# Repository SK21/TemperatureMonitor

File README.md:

# TemperatureMonitor

Temperature Monitor reads temperatures from DS18B20 sensors in grain bins. It consists of a server and multiple clients (controlboxes). The server is installed on a PC on the LAN. Each controlbox sends data over wifi to the server. On startup if a network connection can't be made a web page is started at 192.168.4.1 . 
  
Hookup Schematic:
</img> 

TMarduino can use a DS2482 1-Wire Master. It is a device to connect to 1-Wire networks for improved performance. A DS2482 breakout is available at https://www.artekit.eu/products/breakout-boards/io/ak-ds2482s-100/

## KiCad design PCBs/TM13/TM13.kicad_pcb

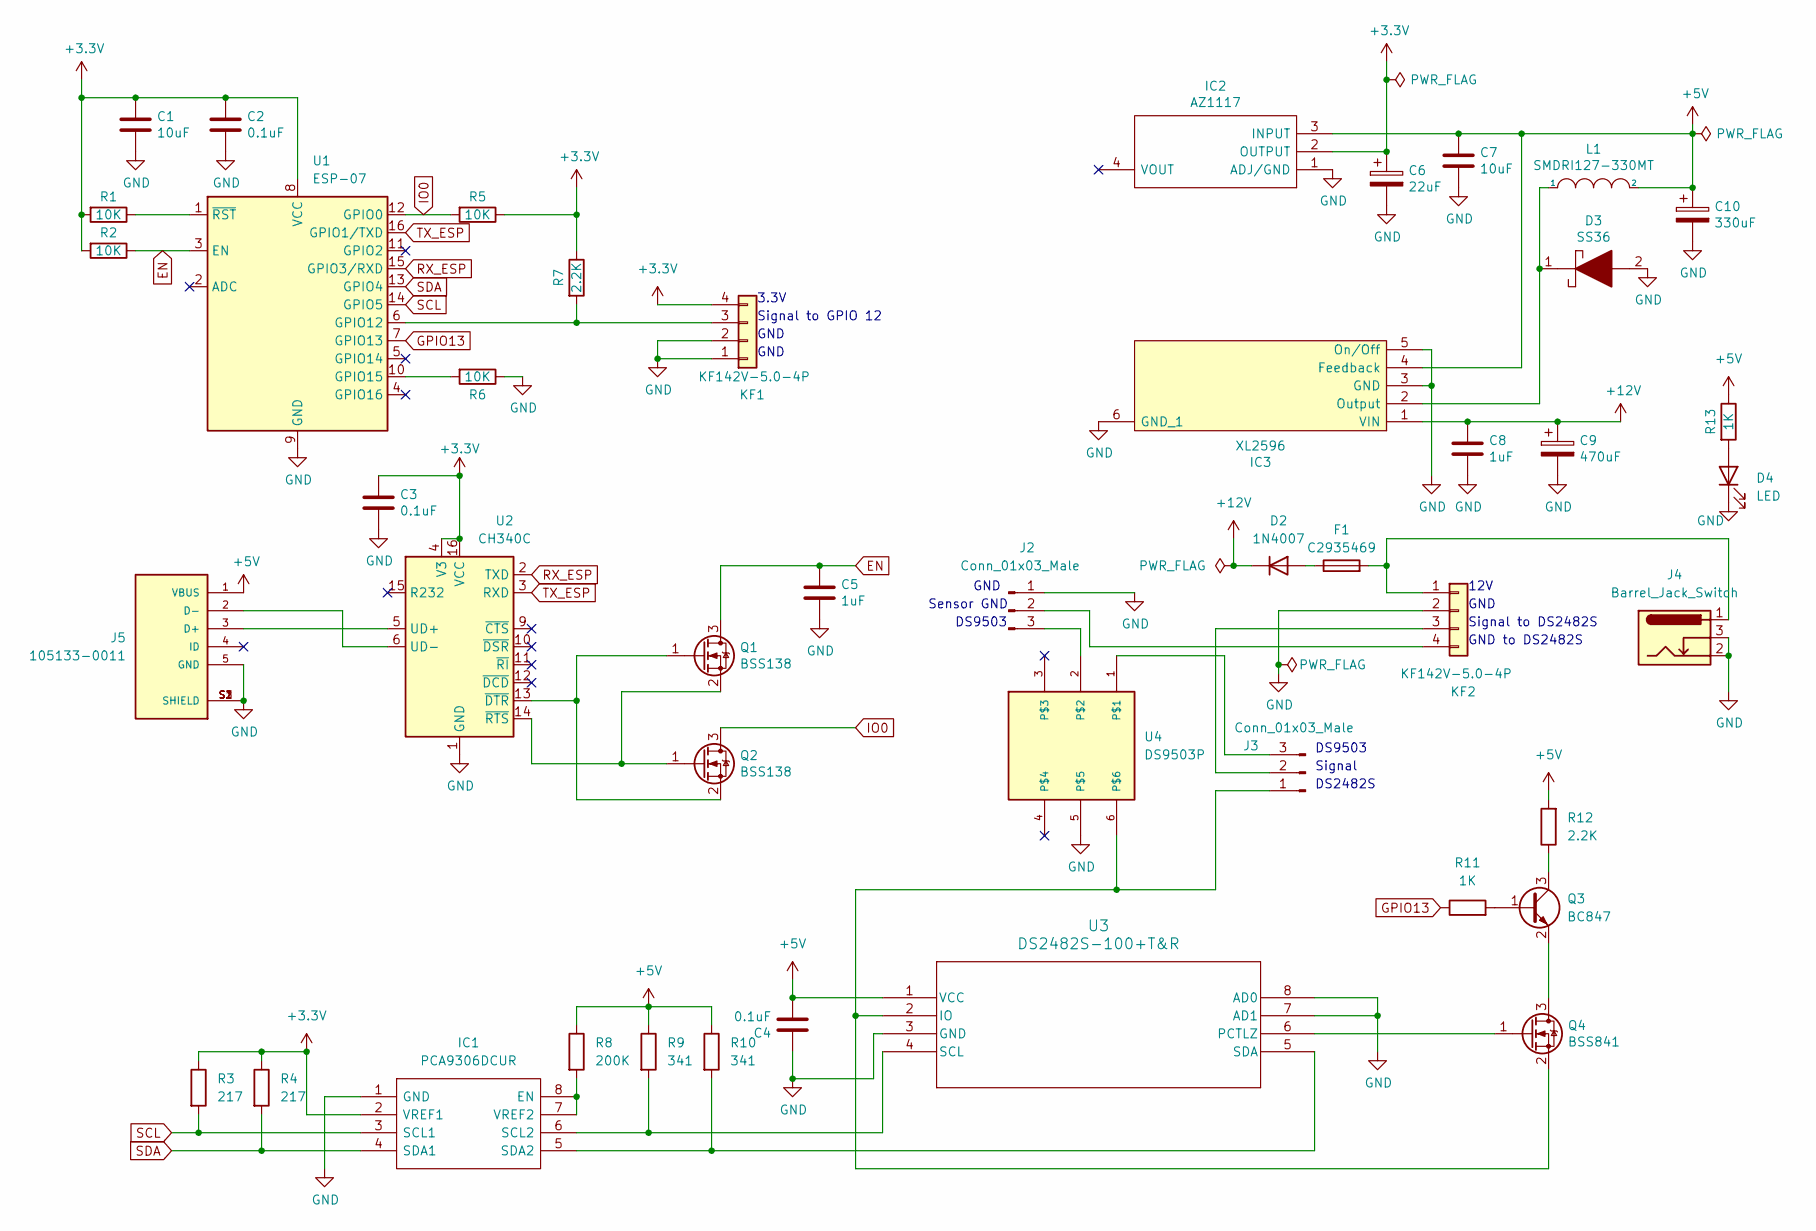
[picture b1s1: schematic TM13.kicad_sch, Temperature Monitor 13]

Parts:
C1, C7: 10uF; C_0805_2012Metric
C2, C3, C4: 0.1uF; C_0805_2012Metric
C5, C8: 1uF; C_0805_2012Metric
C6: 22uF; C_0805_2012Metric
C9: 470uF; CP_Elec_10x10.5
C10: 330uF; CP_Elec_10x10.5
D2: 1N4007; D_SMA
D3: SS36; SMA(DO-214AC)
D4: LED; LED_0805_2012Metric
F1: C2935469; Fuse_Holder_C2935469
IC1: PCA9306DCUR; Mouser Part Number 595-PCA9306DCUR
IC2: AZ1117; SOT230P700X180-4N; Mouser Part Number 621-AZ1117CH-3.3TRG1
IC3: XL2596; TO263-5L
J2, J3: Conn_01x03_Male; PinHeader_1x03_P2.54mm_Vertical
J4: Barrel_Jack_Switch; BarrelJack_Wuerth_6941xx301002
J5: 105133-0011; MOLEX_105133-0011; PARTREV C
KF1, KF2: KF142V-5.0-4P; KF142V-5.08-4P
L1: SMDRI127-330MT; TMPA1265SP-101MN-D
Q1, Q2: BSS138; SOT-23
Q3: BC847; SOT-23
Q4: BSS841; SOT-23
R1, R2, R5, R6: 10K; R_0603_1608Metric
R3, R4: 217; R_0603_1608Metric
R7, R12: 2.2K; R_0603_1608Metric
R8: 200K; R_0603_1608Metric
R9, R10: 341; R_0603_1608Metric
R11, R13: 1K; R_0603_1608Metric
U1: ESP-07; ESP-07S
U2: CH340C; SOIC-16_3.9x9.9mm_P1.27mm
U3: DS2482S-100+T&R; 21-0041B_8_MXM
U4: DS9503P; TSO6C

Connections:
+3.3V: C1.1, C2.1, C3.1, C6.1, IC1.2 (VREF1), IC2.2 (OUTPUT), KF1.4, R1.2, R2.2, R3.1, R4.1, R5.1, R7.1, U1.8 (VCC), U2.4 (V3), U2.16 (VCC)
+5V: C4.2, C7.1, C10.1, IC2.3 (INPUT), IC3.4 (Feedback), J5.1 (VBUS), L1.2, R8.1, R9.1, R10.1, R12.2, R13.1, U3.1 (VCC)
+12V: C8.1, C9.1, D2.1 (K), IC3.1 (VIN)
EN: C5.1, Q1.3 (D), R2.1, U1.3 (EN)
GND: C1.2, C2.2, C3.2, C4.1, C5.2, C6.2, C7.2, C8.2, C9.2, C10.2, D3.2, D4.1 (K), IC1.1 (GND), IC2.1 (ADJ/GND), IC3.3 (GND), IC3.5 (On/Off), IC3.6 (GND_1), J2.1, J4.2, J4.3, J5.5 (GND), J5.S1 (SHIELD), J5.S2 (SHIELD), J5.S3 (SHIELD), KF1.1, KF1.2, KF2.2, R6.1, U1.9 (GND), U2.1 (GND), U3.3 (GND), U3.7 (AD1), U3.8 (AD0), U4.5
GPIO13: R11.1, U1.7 (GPIO13)
IO0: Q2.3 (D), R5.2, U1.12 (GPIO0)
unnamed: D2.2 (A), F1.1
unnamed: D4.2 (A), R13.2
unnamed: IC1.7 (VREF2), IC1.8 (EN), R8.2
unnamed: IC1.6 (SCL2), R9.2, U3.4 (SCL)
unnamed: IC1.5 (SDA2), R10.2, U3.5 (SDA)
unnamed: D3.1, IC3.2 (Output), L1.1
unnamed: J2.2, KF2.4
unnamed: J2.3, U4.2
unnamed: J3.1, Q4.2 (S), U3.2 (IO), U4.6
unnamed: J3.2, KF2.3
unnamed: J3.3, U4.1
unnamed: J5.3 (D+), U2.5 (UD+)
unnamed: J5.2 (D-), U2.6 (UD-)
unnamed: KF1.3, R7.2, U1.6 (GPIO12)
unnamed: F1.2, J4.1, KF2.1
unnamed: Q1.1 (G), Q2.2 (S), U2.13 (~DTR)
unnamed: Q1.2 (S), Q2.1 (G), U2.14 (~RTS)
unnamed: Q3.1 (B), R11.2
unnamed: Q3.3 (C), R12.1
unnamed: Q3.2 (E), Q4.3 (D)
unnamed: Q4.1 (G), U3.6 (PCTLZ)
unnamed: R6.2, U1.10 (GPIO15)
unnamed: R1.1, U1.1 (~RST)
RX_ESP: U1.15 (GPIO3/RXD), U2.2 (TXD)
SCL: IC1.3 (SCL1), R3.2, U1.14 (GPIO5)
SDA: IC1.4 (SDA1), R4.2, U1.13 (GPIO4)
TX_ESP: U1.16 (GPIO1/TXD), U2.3 (RXD)

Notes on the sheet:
Signal to DS2482S
Sensor GND
GND
DS9503
DS2482S
Signal
12V
GND to DS2482S
Signal to GPIO 12
3.3V

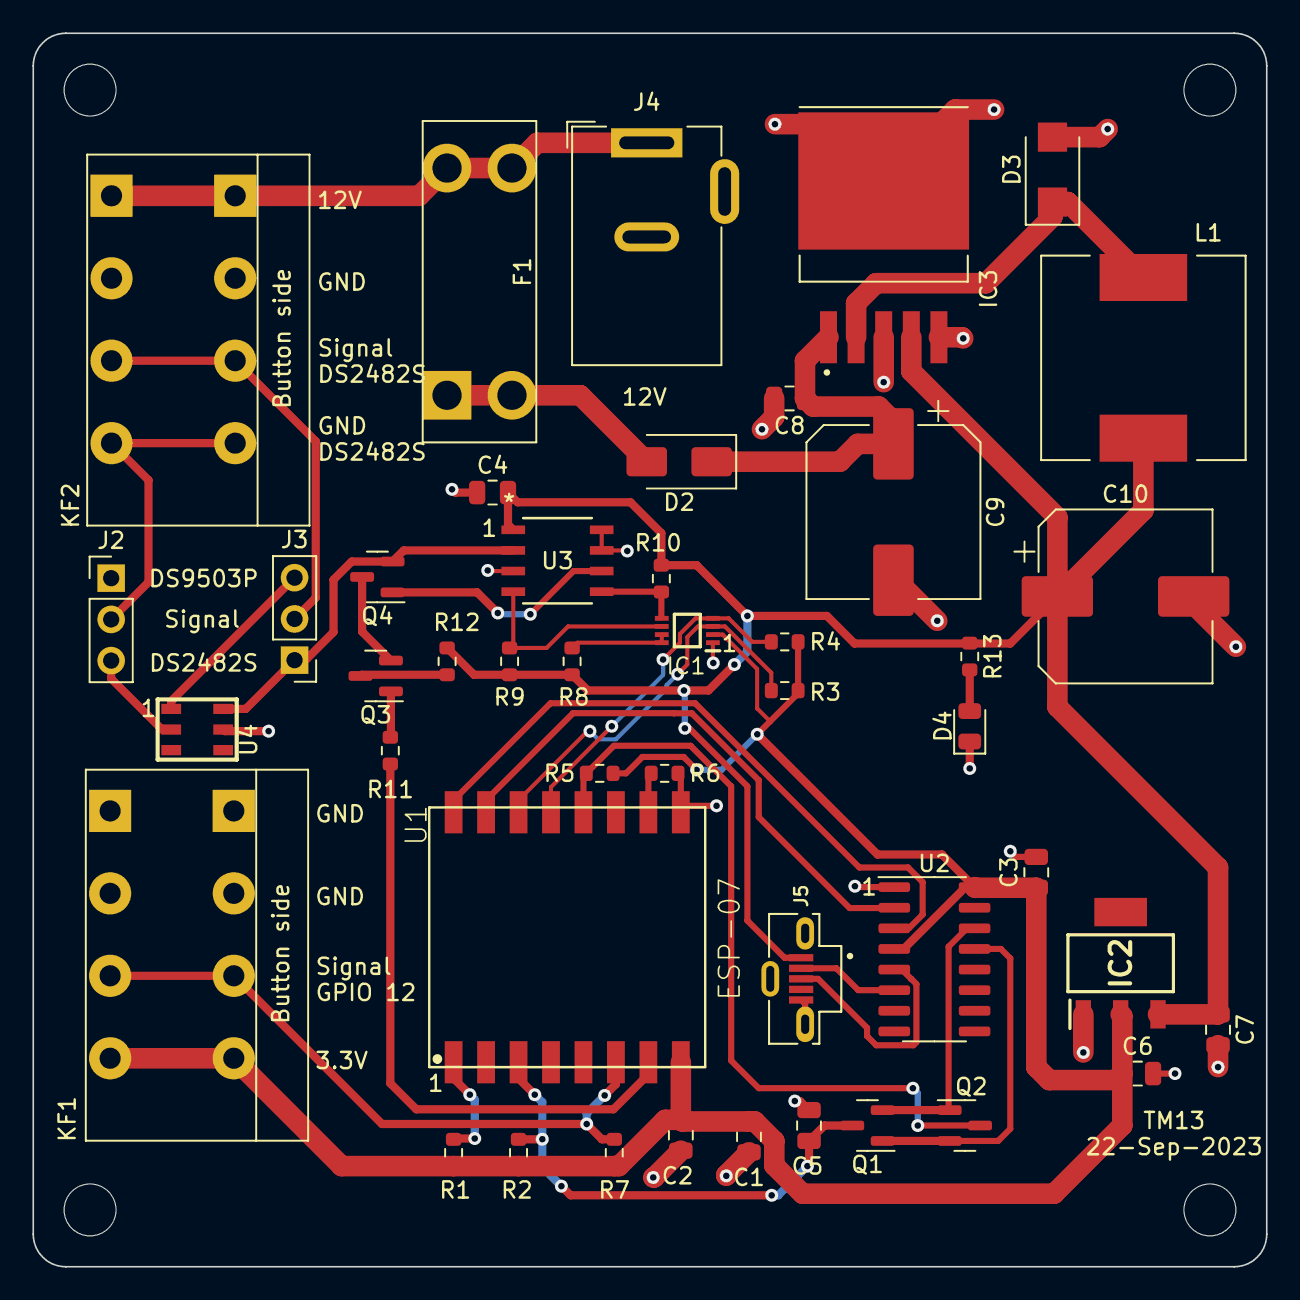
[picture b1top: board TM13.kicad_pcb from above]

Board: 2 copper layers, 76.0 x 76.0 mm, 45 parts (0 on the bottom side), 34 nets.

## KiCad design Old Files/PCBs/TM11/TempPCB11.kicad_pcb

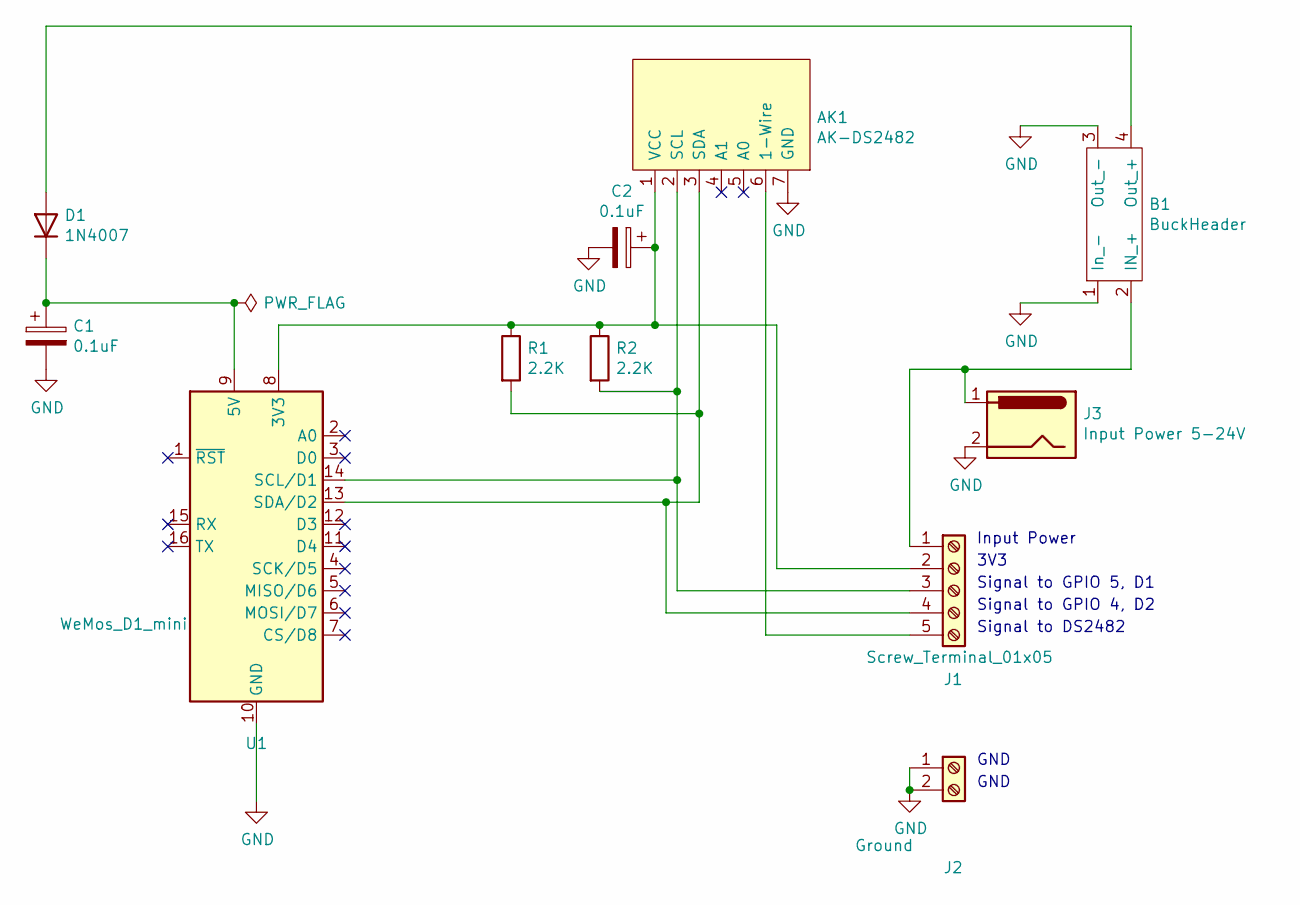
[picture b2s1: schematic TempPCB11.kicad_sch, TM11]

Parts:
AK1: AK-DS2482
B1: BuckHeader; LM2596_Buck_Header
C1, C2: 0.1uF; C_Disc_D5.0mm_W2.5mm_P2.50mm
D1: 1N4007; D_DO-41_SOD81_P10.16mm_Horizontal
J1: Screw_Terminal_01x05; TerminalBlock_Phoenix_PT-1,5-5-5.0-H_1x05_P5.00mm_Horizontal
J2: Ground; TerminalBlock_Phoenix_PT-1,5-2-5.0-H_1x02_P5.00mm_Horizontal
J3: Input Power 5-24V; Uxcell_DC_power_jack
R1, R2: 2.2K; R_Axial_DIN0207_L6.3mm_D2.5mm_P10.16mm_Horizontal
U1: WeMos_D1_mini; WEMOS_D1_mini_light

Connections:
GND: AK1.7 (GND), B1.1 (In_-), B1.3 (Out_-), C1.2, C2.2, J2.1, J2.2, J3.2, U1.10 (GND)
unnamed: AK1.1 (VCC), C2.1, J1.2, R1.1, R2.1, U1.8 (3V3)
unnamed: AK1.2 (SCL), J1.3, R2.2, U1.14 (SCL/D1)
unnamed: AK1.3 (SDA), J1.4, R1.2, U1.13 (SDA/D2)
unnamed: AK1.6 (1-Wire), J1.5
unnamed: B1.2 (IN_+), J1.1, J3.1
unnamed: B1.4 (Out_+), D1.2 (A)
unnamed: C1.1, D1.1 (K), U1.9 (5V)

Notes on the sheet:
3V3
Signal to GPIO 5, D1
Signal to GPIO 4, D2
Signal to DS2482
GND
Input Power

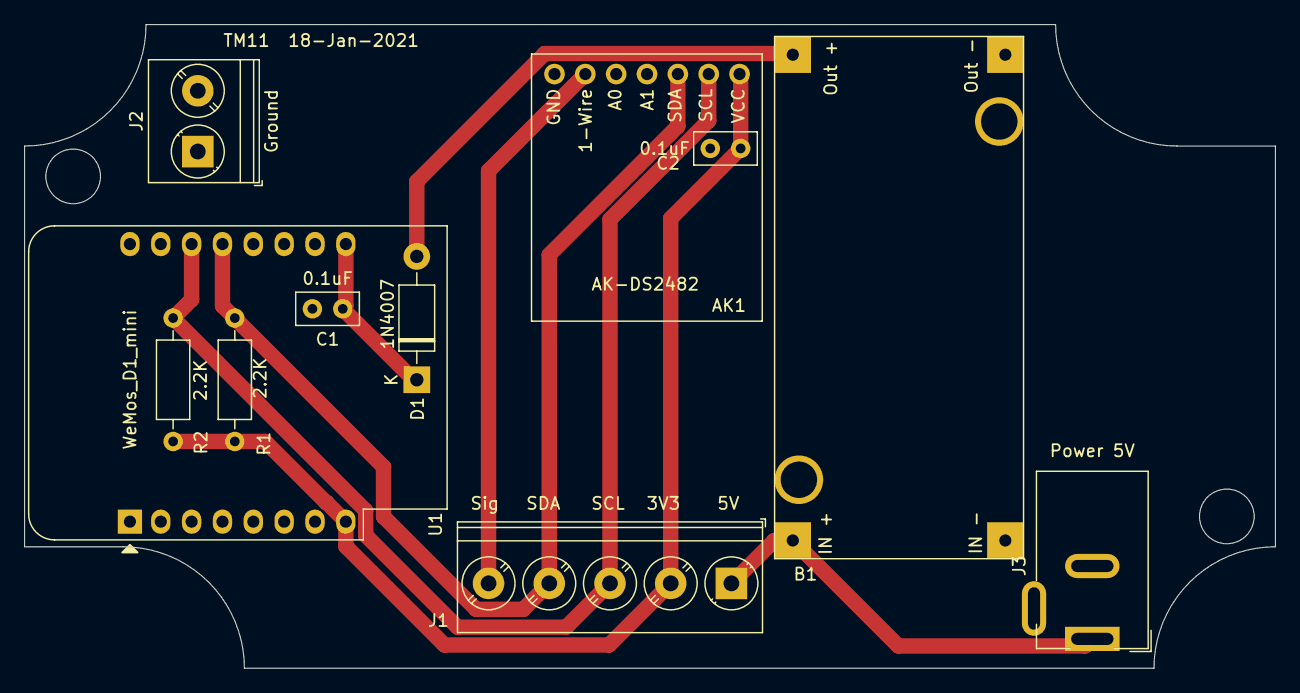
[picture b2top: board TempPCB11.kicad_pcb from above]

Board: 2 copper layers, 103.0 x 53.0 mm, 13 parts (0 on the bottom side), 8 nets.

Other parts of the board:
 : MountingHole_3.2mm_M3
 #2: MountingHole_3.2mm_M3

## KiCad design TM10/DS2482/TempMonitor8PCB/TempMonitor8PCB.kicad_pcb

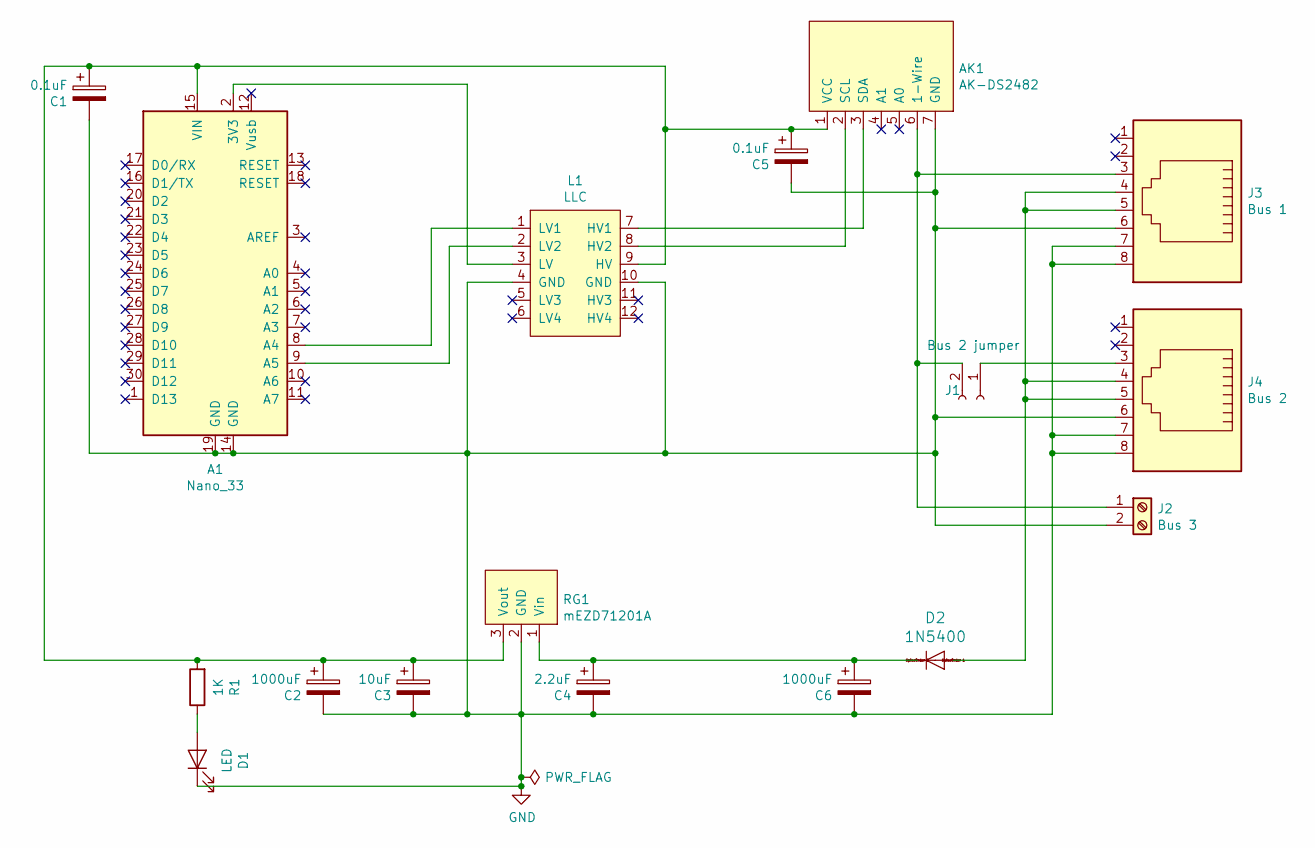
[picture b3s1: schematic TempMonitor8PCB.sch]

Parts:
A1: Nano_33
AK1: AK-DS2482
C1, C5: 0.1uF; C_Disc_D5.0mm_W2.5mm_P2.50mm
C2, C6: 1000uF; CP_Radial_D10.0mm_P5.00mm
C3: 10uF; C_Disc_D5.0mm_W2.5mm_P2.50mm
C4: 2.2uF; C_Disc_D5.0mm_W2.5mm_P2.50mm
D1: LED; LED_D3.0mm
D2: 1N5400
J1: Bus 2 jumper; PinHeader_1x02_P2.54mm_Vertical
J2: Bus 3; Phoenix_2_pin_5mm_terminal_block
J3: Bus 1; RJ45_Amphenol_54602-x08_Horizontal
J4: Bus 2; RJ45_Amphenol_54602-x08_Horizontal
L1: LLC
R1: 1K; R_Axial_DIN0207_L6.3mm_D2.5mm_P10.16mm_Horizontal
RG1: mEZD71201A

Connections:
GND: A1.14 (GND), A1.19 (GND), AK1.7 (GND), C1.2, C2.2, C3.2, C4.2, C5.2, C6.2, D1.1 (K), J2.2, J3.6, J3.7, J3.8, J4.6, J4.7, J4.8, L1.4 (GND), L1.10 (GND), RG1.2 (GND)
unnamed: A1.2 (3V3), L1.3 (LV)
unnamed: A1.8 (A4), L1.1 (LV1)
unnamed: A1.9 (A5), L1.2 (LV2)
unnamed: A1.15 (VIN), AK1.1 (VCC), C1.1, C2.1, C3.1, C5.1, L1.9 (HV), R1.2, RG1.3 (Vout)
unnamed: AK1.2 (SCL), L1.8 (HV2)
unnamed: AK1.3 (SDA), L1.7 (HV1)
unnamed: AK1.6 (1-Wire), J1.2, J2.1, J3.3
unnamed: C4.1, C6.1, D2.C, RG1.1 (Vin)
unnamed: D1.2 (A), R1.1
unnamed: D2.A, J3.4, J3.5, J4.4, J4.5
unnamed: J1.1, J4.3

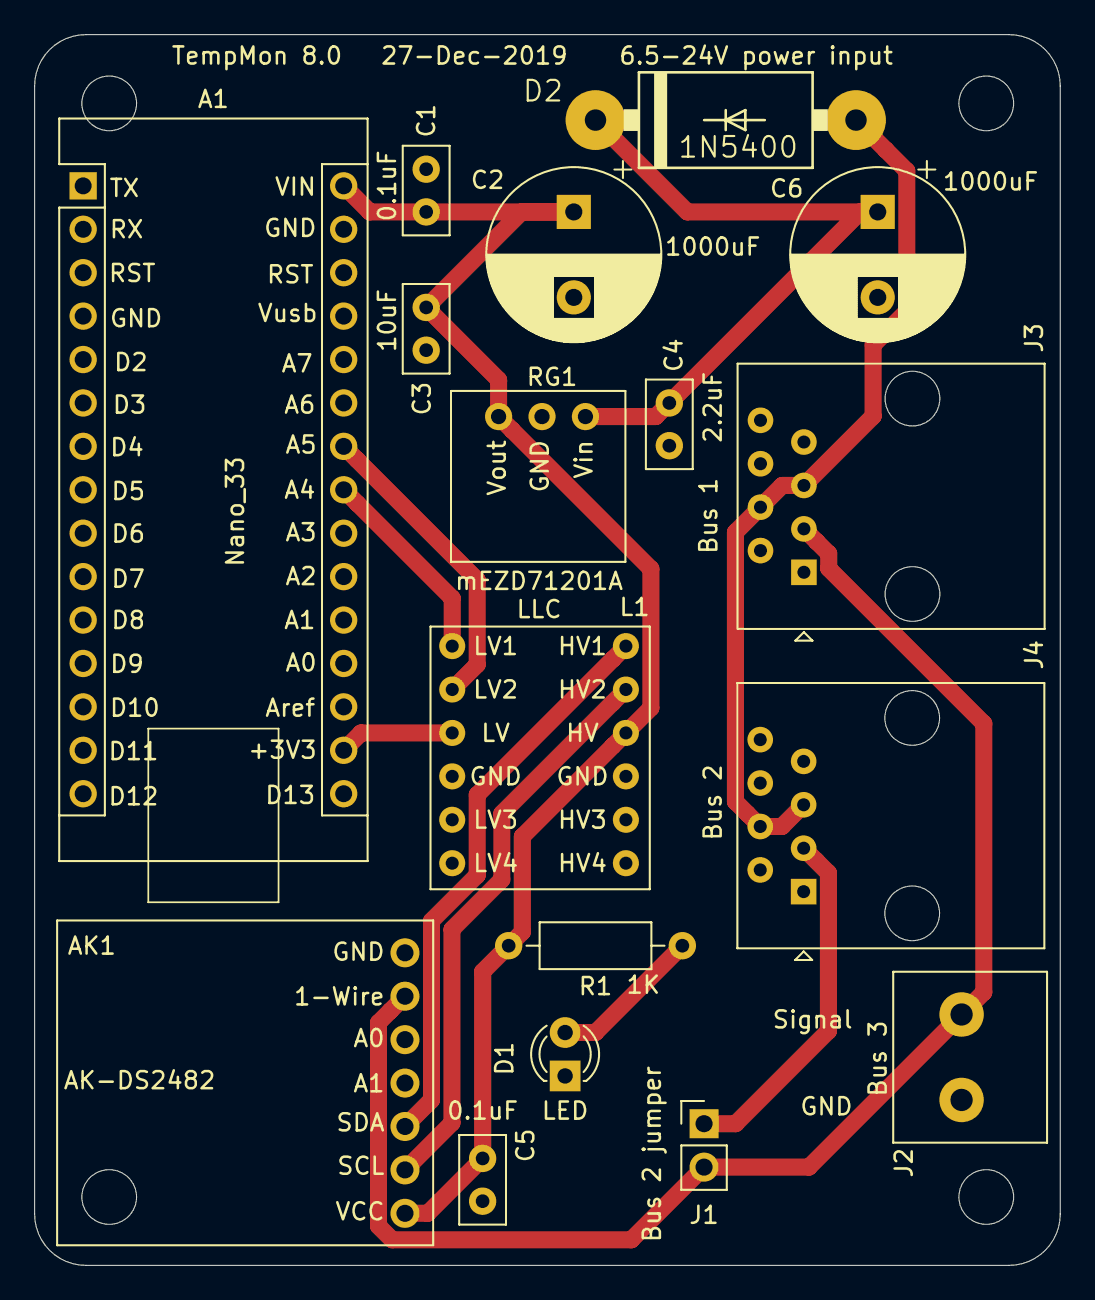
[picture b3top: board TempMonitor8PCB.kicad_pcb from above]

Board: 2 copper layers, 60.0 x 72.0 mm, 17 parts (0 on the bottom side), 12 nets.

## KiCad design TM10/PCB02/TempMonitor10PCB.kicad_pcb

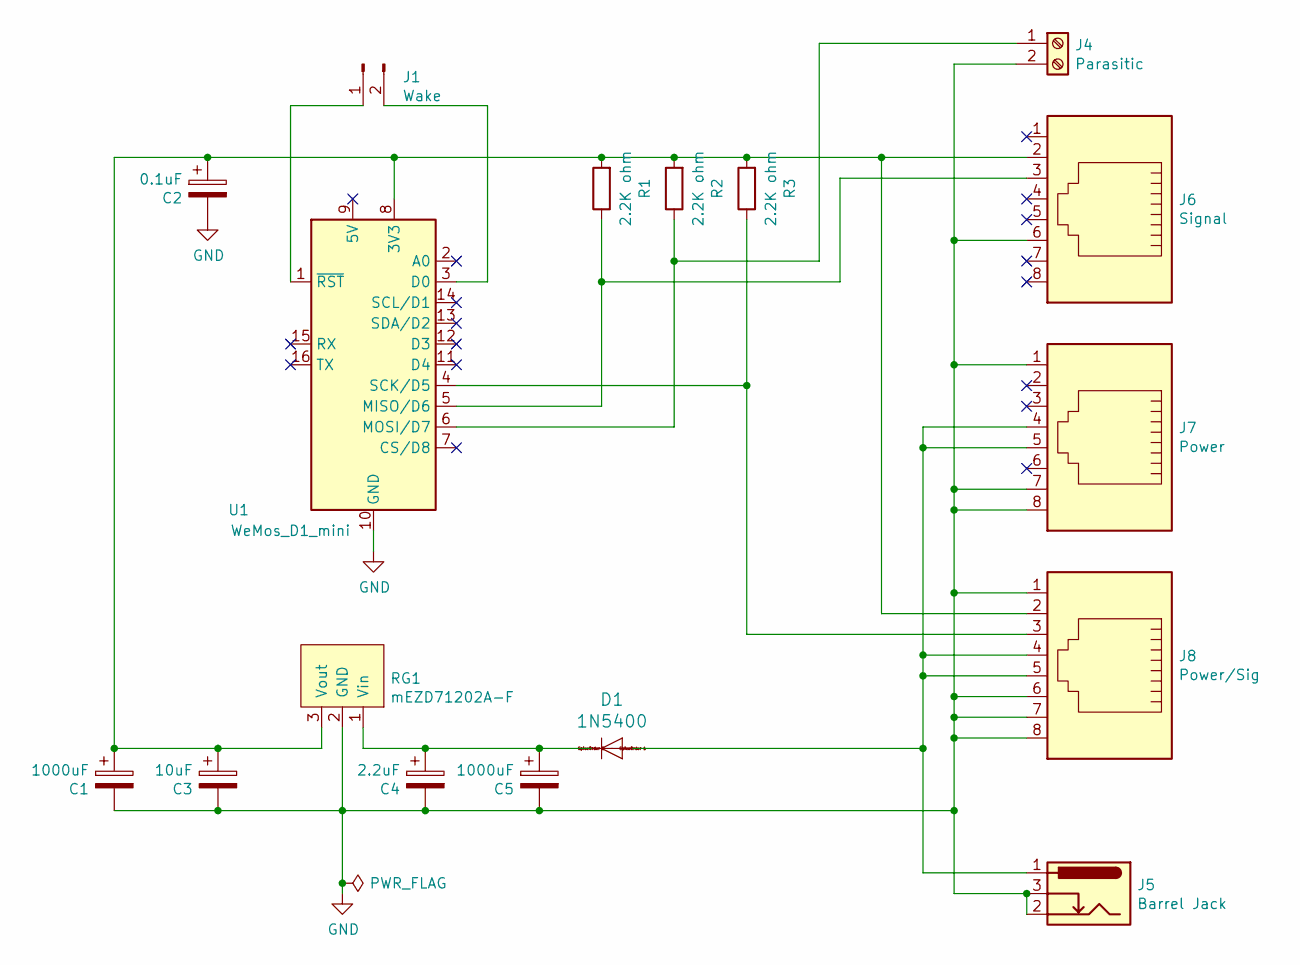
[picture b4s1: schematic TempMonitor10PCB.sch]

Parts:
C1, C5: 1000uF; CP_Radial_D10.0mm_P5.00mm
C2: 0.1uF; C_Disc_D5.0mm_W2.5mm_P2.50mm
C3: 10uF; C_Disc_D5.0mm_W2.5mm_P2.50mm
C4: 2.2uF; C_Disc_D5.0mm_W2.5mm_P2.50mm
D1: 1N5400
J1: Wake; PinHeader_1x02_P2.54mm_Vertical
J4: Parasitic; TerminalBlock_Phoenix_PT-1,5-2-5.0-H_1x02_P5.00mm_Horizontal
J5: Barrel Jack; Uxcell_DC_power_jack
J6: Signal; RJ45_Amphenol_54602-x08_Horizontal
J7: Power; RJ45_Amphenol_54602-x08_Horizontal
J8: Power/Sig; RJ45_Amphenol_54602-x08_Horizontal
R1, R2, R3: 2.2K ohm; R_Axial_DIN0207_L6.3mm_D2.5mm_P10.16mm_Horizontal
RG1: mEZD71202A-F; mEZD71201A
U1: WeMos_D1_mini; WEMOS_D1_mini_light

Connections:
GND: C1.2, C2.2, C3.2, C4.2, C5.2, J4.2, J5.2, J5.3, J6.6, J7.1, J7.7, J7.8, J8.1, J8.6, J8.7, J8.8, RG1.2 (GND), U1.10 (GND)
unnamed: C1.1, C2.1, C3.1, J6.2, J8.2, R1.2, R2.2, R3.2, RG1.3 (Vout), U1.8 (3V3)
unnamed: C4.1, C5.1, D1.C, RG1.1 (Vin)
unnamed: D1.A, J5.1, J7.4, J7.5, J8.4, J8.5
unnamed: J1.1, U1.1 (~RST)
unnamed: J1.2, U1.3 (D0)
unnamed: J4.1, R2.1, U1.6 (MOSI/D7)
unnamed: J6.3, R1.1, U1.5 (MISO/D6)
unnamed: J8.3, R3.1, U1.4 (SCK/D5)

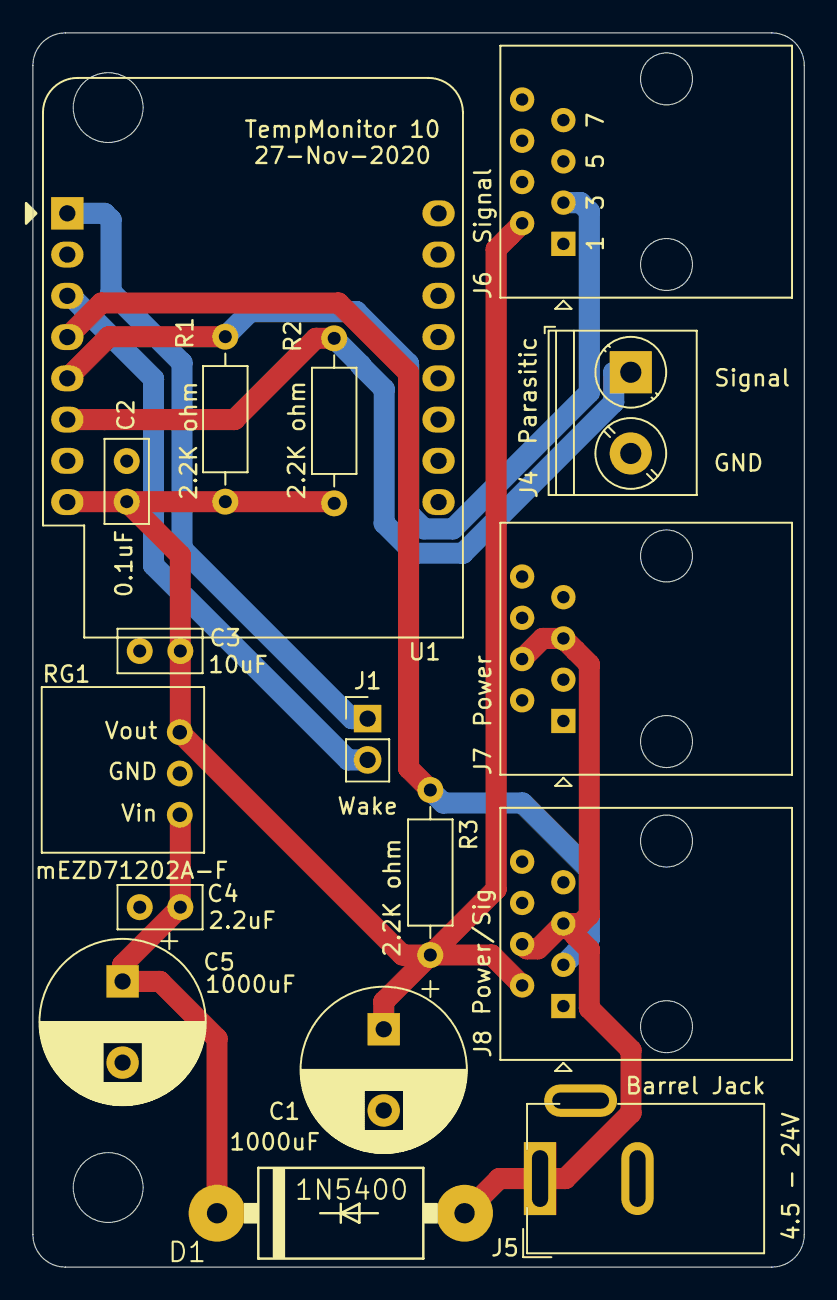
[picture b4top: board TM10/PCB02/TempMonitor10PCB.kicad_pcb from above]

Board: 2 copper layers, 47.5 x 76.0 mm, 17 parts (0 on the bottom side), 9 nets.

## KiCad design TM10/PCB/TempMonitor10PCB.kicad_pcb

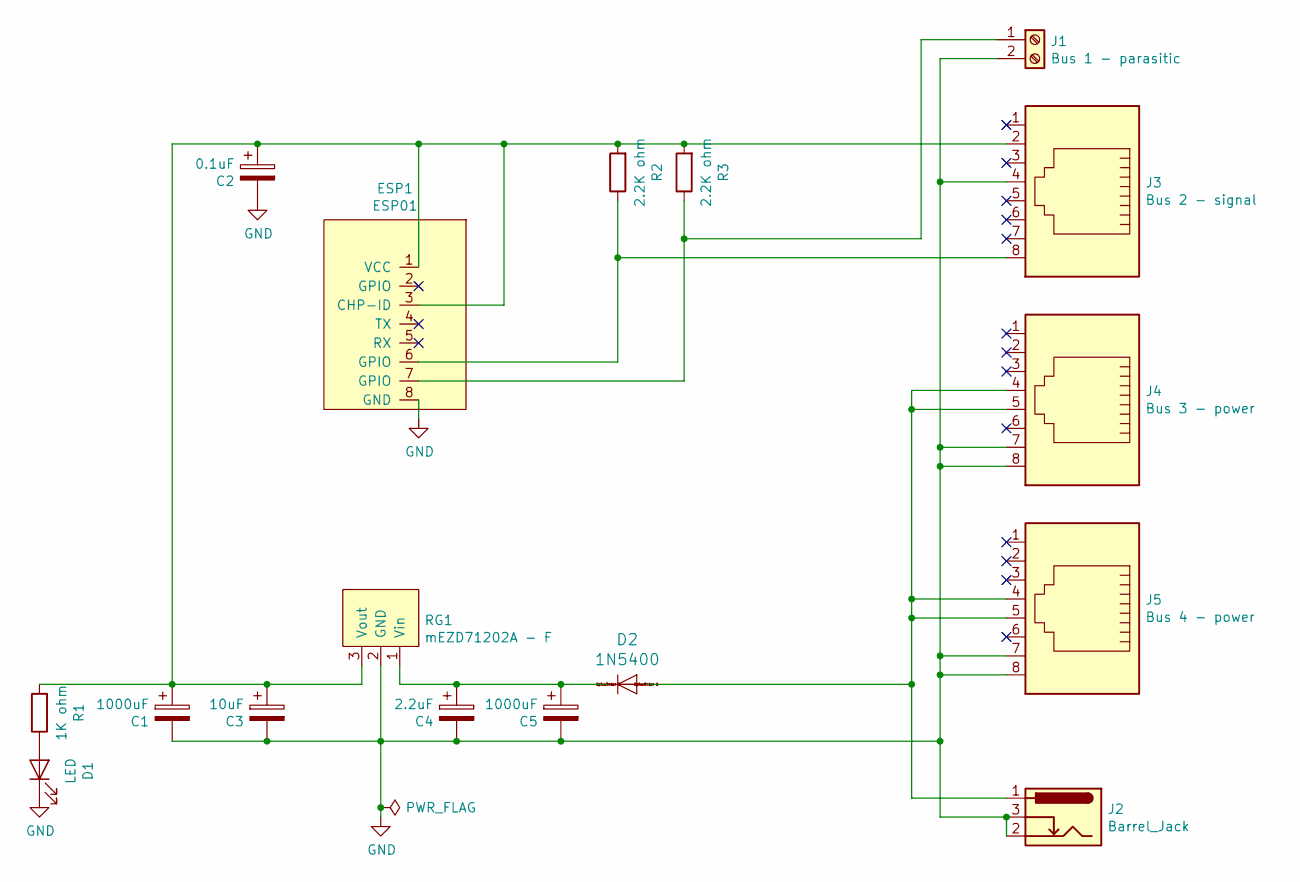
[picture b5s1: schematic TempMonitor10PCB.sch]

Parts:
C1, C5: 1000uF; CP_Radial_D10.0mm_P5.00mm
C2: 0.1uF; C_Disc_D5.0mm_W2.5mm_P2.50mm
C3: 10uF; C_Disc_D5.0mm_W2.5mm_P2.50mm
C4: 2.2uF; C_Disc_D5.0mm_W2.5mm_P2.50mm
D1: LED; LED_D3.0mm
D2: 1N5400
ESP1: ESP01
J1: Bus 1 - parasitic; TerminalBlock_Phoenix_PT-1,5-2-5.0-H_1x02_P5.00mm_Horizontal
J2: Barrel_Jack; Uxcell_DC_power_jack
J3: Bus 2 - signal; RJ45_Amphenol_54602-x08_Horizontal
J4: Bus 3 - power; RJ45_Amphenol_54602-x08_Horizontal
J5: Bus 4 - power; RJ45_Amphenol_54602-x08_Horizontal
R1: 1K ohm; R_Axial_DIN0207_L6.3mm_D2.5mm_P10.16mm_Horizontal
R2, R3: 2.2K ohm; R_Axial_DIN0207_L6.3mm_D2.5mm_P10.16mm_Horizontal
RG1: mEZD71202A - F; mEZD71201A

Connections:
GND: C1.2, C2.2, C3.2, C4.2, C5.2, D1.1 (K), ESP1.8 (GND), J1.2, J2.2, J2.3, J3.4, J4.7, J4.8, J5.7, J5.8, RG1.2 (GND)
unnamed: C1.1, C2.1, C3.1, ESP1.1 (VCC), ESP1.3 (CHP-ID), J3.2, R1.2, R2.2, R3.2, RG1.3 (Vout)
unnamed: C4.1, C5.1, D2.C, RG1.1 (Vin)
unnamed: D1.2 (A), R1.1
unnamed: D2.A, J2.1, J4.4, J4.5, J5.4, J5.5
unnamed: ESP1.6 (GPIO), J3.8, R2.1
unnamed: ESP1.7 (GPIO), J1.1, R3.1

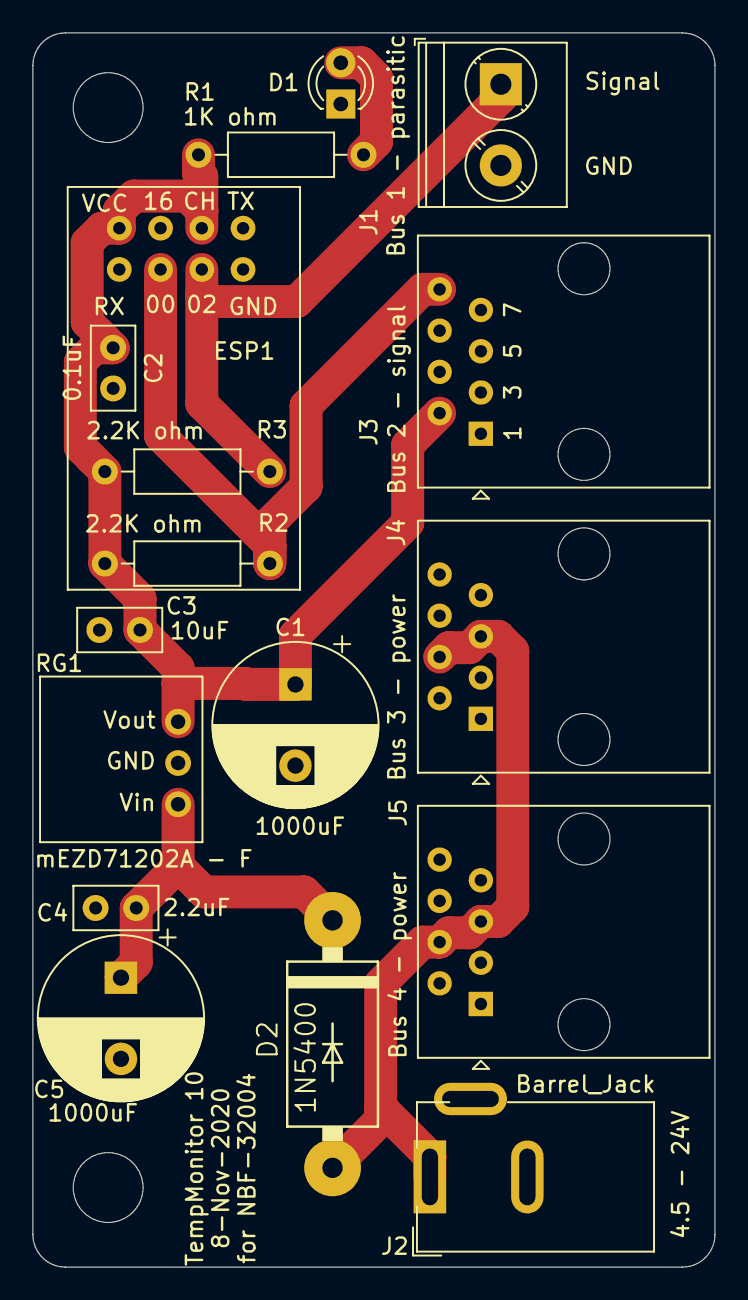
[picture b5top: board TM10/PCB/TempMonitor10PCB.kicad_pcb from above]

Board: 2 copper layers, 42.0 x 76.0 mm, 17 parts (0 on the bottom side), 7 nets.

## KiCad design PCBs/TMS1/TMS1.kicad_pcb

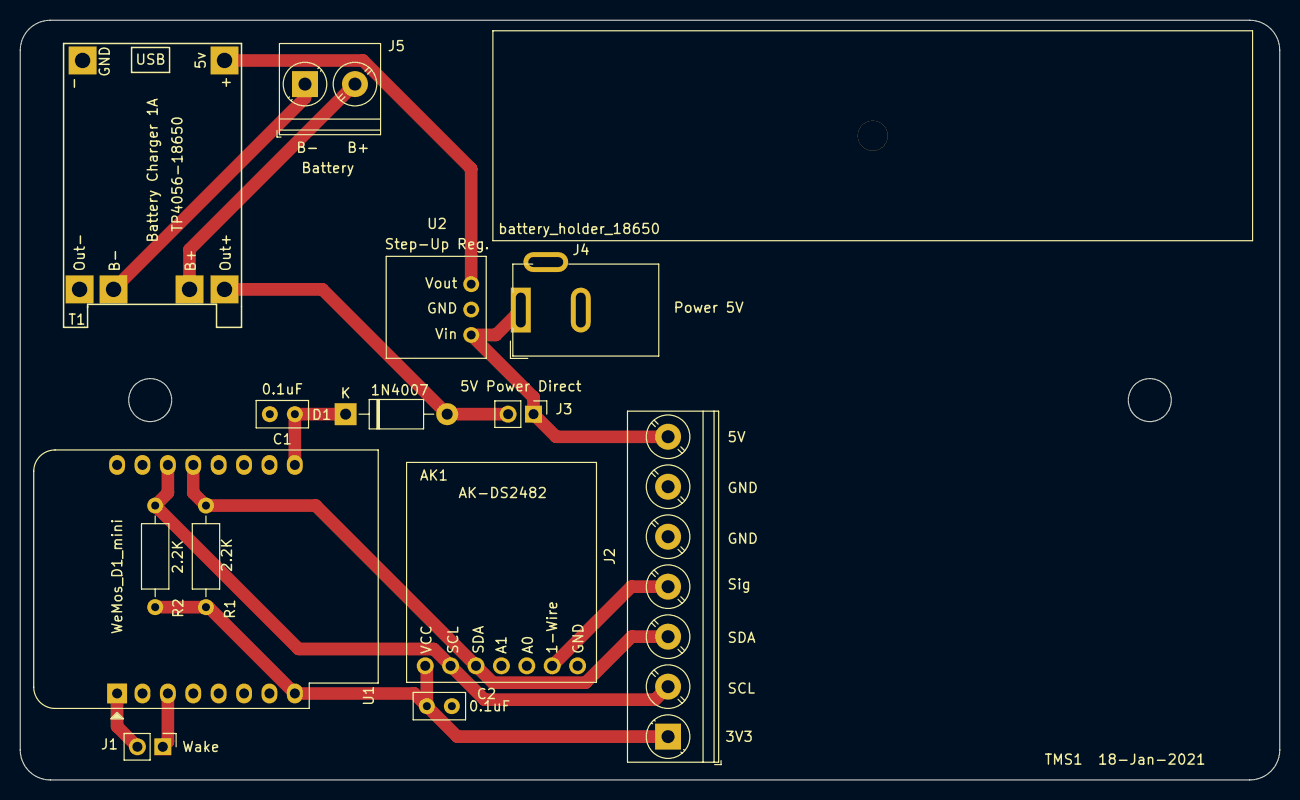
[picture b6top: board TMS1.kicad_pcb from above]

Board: 2 copper layers, 126.0 x 76.0 mm, 17 parts (0 on the bottom side), 13 nets.

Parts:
 : MountingHole_4.3mm_M4
 #2: MountingHole_4.3mm_M4
 #3: battery_holder_18650
AK1: AK-DS2482
C1, C2: 0.1uF; C_Disc_D5.0mm_W2.5mm_P2.50mm
D1: 1N4007; D_DO-41_SOD81_P10.16mm_Horizontal
J1: Wake; PinHeader_1x02_P2.54mm_Vertical
J2: Screw_Terminal_01x07; TerminalBlock_Phoenix_PT-1,5-7-5.0-H_1x07_P5.00mm_Horizontal
J3: 5V Power Direct; PinHeader_1x02_P2.54mm_Vertical
J4: Power 5V; Uxcell_DC_power_jack
J5: Battery; TerminalBlock_Phoenix_PT-1,5-2-5.0-H_1x02_P5.00mm_Horizontal
R1, R2: 2.2K; R_Axial_DIN0207_L6.3mm_D2.5mm_P10.16mm_Horizontal
T1: TP4056-18650
U1: WeMos_D1_mini; WEMOS_D1_mini_light
U2: Step-Up Reg.; mEZD71201A

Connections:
GND: AK1.7, C1.2, C2.2, J2.5, J2.6, J4.2, T1.2, T1.4, U1.10, U2.2
unnamed: AK1.1, C2.1, J2.1, R1.1, R2.1, U1.8
unnamed: AK1.2, J2.2, R2.2, U1.14
unnamed: AK1.3, J2.3, R1.2, U1.13
unnamed: AK1.6, J2.4
unnamed: C1.1, D1.1, U1.9
unnamed: D1.2, J3.2, T1.3
unnamed: J1.1, U1.3
unnamed: J1.2, U1.1
unnamed: J2.7, J3.1, J4.1, U2.1
unnamed: J5.1, T1.6
unnamed: J5.2, T1.5
unnamed: T1.1, U2.3

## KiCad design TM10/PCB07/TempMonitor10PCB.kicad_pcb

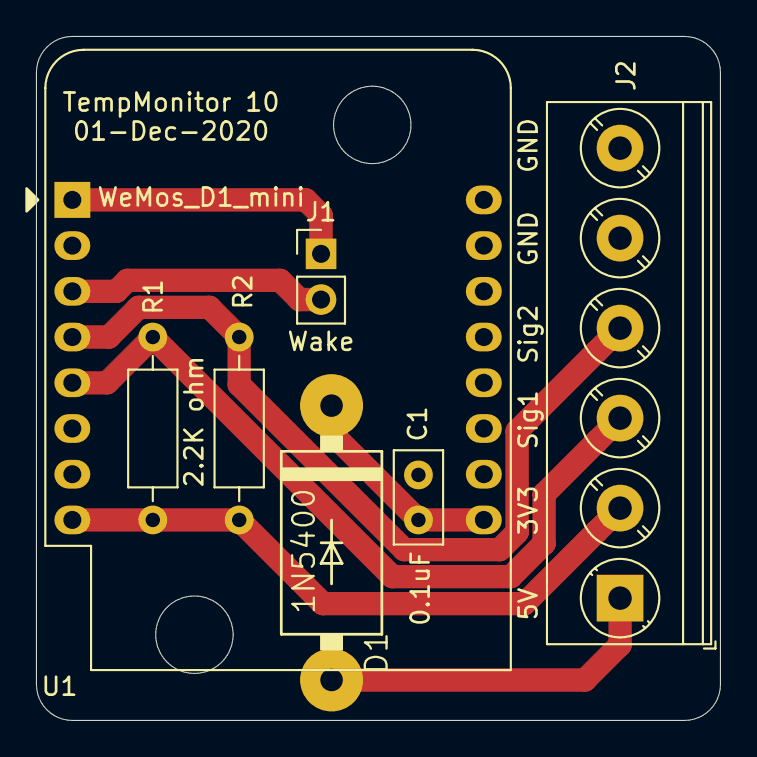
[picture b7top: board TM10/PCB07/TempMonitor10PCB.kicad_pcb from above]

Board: 2 copper layers, 38.0 x 38.0 mm, 7 parts (0 on the bottom side), 8 nets.

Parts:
C1: 0.1uF; C_Disc_D5.0mm_W2.5mm_P2.50mm
D1: 1N5400
J1: Wake; PinHeader_1x02_P2.54mm_Vertical
J2: Screw_Terminal_01x06; TerminalBlock_Phoenix_PT-1,5-6-5.0-H_1x06_P5.00mm_Horizontal
R1, R2: 2.2K ohm; R_Axial_DIN0207_L6.3mm_D2.5mm_P10.16mm_Horizontal
U1: WeMos_D1_mini; WEMOS_D1_mini_light

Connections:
GND: C1.2, J2.5, J2.6, U1.10
unnamed: C1.1, D1.C, U1.9
unnamed: D1.A, J2.1
unnamed: J1.1, U1.1
unnamed: J1.2, U1.3
unnamed: J2.2, R1.2, R2.2, U1.8
unnamed: J2.3, R1.1, U1.5
unnamed: J2.4, R2.1, U1.4

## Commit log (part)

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2020-11-23 Updated files.
2020-11-27 Wemos D1 mini version
2020-11-28 fixed sensor setdata sub, added webpage
2020-11-29 added pictures
2020-12-04 design change due to magic smoke
2020-12-05 change controlbox ID from config page
2020-12-27 web pages, sleep, OTA, etc.
2021-01-09 Two's complement temp conversion, clean-up files
2021-01-09 Two's complement temp conversion
2021-01-09 DS2482, Nano 33 version
2021-01-09 Two's Complement info
2021-01-10 fix sleep time calculation
2021-01-10 update sleep time info
2021-01-11 updated sleep remaining calculation
2021-01-16 DS2482, Wemos D1 mini version, to replace buggy Nano 33 wifi
2021-01-21 added option for DS2482, reorganized files
2021-01-21 update install
2021-01-23 updated 2s complement cals, added CRC8
2021-01-23 updated 2s complement, added CRC8
2022-12-07 update web GUI
    Improved web GUI for use with VB6 server.
2023-08-11 update folders
2023-08-12 update folders, fix webpage temps
2023-11-13 TM13 pcb
2023-11-13 read temps every hour
2023-11-14 fix timer loop
2023-11-15 no auto reconnect, trim webserver input
2023-11-21 move old files
2023-11-22 c# server
2023-11-23 load/save database connection
2023-11-23 add pgn
2023-11-24 update pcb
2023-11-24 update quote description
2024-07-23 disconnect station mode when not in use
2024-07-24 prevent unresponsive web page
2024-08-02 update hex file
2026-03-08 New version
2026-03-08 update module code
2026-03-08 pgns
2026-03-08 fix pgns
2026-03-08 udp instead of tcp
2026-03-09 remove unused code
2026-03-09 temperature app
2026-03-09 classes added
2026-03-09 test run
2026-03-09 fix connection
2026-03-09 graphing
2026-03-10 change db location
2026-03-10 fix ui spacing
2026-03-10 change font
2026-03-10 rename app
2026-03-10 convertor form
2026-03-10 ota update
2026-03-10 fix convert sensor data
2026-03-10 update frequency
2026-03-10 add button
2026-03-10 change update frequency
2026-03-10 bad packet logger
2026-03-10 Simplify README description of Temperature Monitor
    Removed redundant information about controlbox operation and power sources.
2026-03-11 reorganize
2026-03-11 change date format
2026-03-11 update commands
2026-03-11 fix comm
2026-03-12 update web page, change temp button function
2026-03-12 update csv file
2026-03-12 update user manual
2026-03-12 Discover button
2026-03-14 print graph, change database locking
2026-03-15 fix load error, update user manual
2026-03-16 clean-up files
2026-03-16 remove label
2026-05-08 fix database index error
